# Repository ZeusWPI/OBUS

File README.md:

# Ontmijnen van een Bom vereist Uitstekende Samenwerking

You see an armed time bomb but don't know how to disarm it. Your friends found a manual to defuse the bomb and you have them on call. This is the premise of the game OBUS, a hardware project by [Zeus WPI](https://zeus.ugent.be). Inspired by the amazing software game [Keep Talking and Nobody Explodes](https://www.keeptalkinggame.com/).

## Get started writing a module

These are the instructions for building your own OBUS module with an Arduino Nano v3 and the custom PCB. If
you're using other hardware, you might need to do some things differently.

0. (Read the "[Getting started guide](docs/GETTING_STARTED.md)" to get a general idea of how OBUS works.)
1. [Install](https://www.arduino.cc/en/Guide/#install-the-arduino-desktop-ide) the Arduino IDE.
2. Clone this repository with Git in a permanent location on your drive.
3. Symlink the library: `ln -s /ABSOLUTE/PATH/TO/REPO/lib /PATH/TO/Arduino/libraries/obus`
  (on most Linux distro's, this the Arduino folder is in `$HOME/Arduino`)
4. Follow [these steps](https://github.com/autowp/arduino-mcp2515/#software-usage) to install the CAN library
5. Execute `./src/new_module.sh` to create a new module. When asked for a type, you'll probably want to choose 'puzzle'.
6. Edit the newly generated .ino file, either in the Arduino IDE or in your own editor.
7. In the Arduino IDE, select the correct board (Arduino Nano) and processor (ATmega328P (Old Bootloader)). After that,
   flash your code to the Arduino and test it out.
8. On some Linux distributions, you'll need to prevent BRLTTY from taking over the serial adapter because BRLTTY thinks it's a Braille keyboard. You can do this by uninstalling it (`pacman -R brltty`) or by [disabling it and then rebooting](https://unix.stackexchange.com/questions/670636/unable-to-use-usb-dongle-based-on-usb-serial-converter-chip).
9. If you get permission errors, try adding yourself to the dialout or uucp (Arch Linux) group

## Background
### Game

The game is played by at least two players. The goal is to defuse a bomb,
this is accomplished by defusing every module on that bomb before the bomb
timer runs out.

There are two roles:

- Expert: this person can read the manual about how to defuse the bomb, but cannot see nor interact with the bomb
- Defuser: this person can see and interact with the bomb, but cannot read the manual

These two roles can communicate with each other. To successfully defuse the bomb, they must
communicate efficiently and clearly. If a mistake is made, the team gets a strike.
If they get too many strikes or the timer runs out, the bomb explodes.

## Common wiring between all modules

- CAN-H: red on JST 3 pin connectors, purple on CAN wire
- CAN-L: white on JST 3 pin connectors, brown on CAN wire
- +12V: red on 2 pin JST connector and power wire
- ground: black on 2 pin JST connector, no color on power wire

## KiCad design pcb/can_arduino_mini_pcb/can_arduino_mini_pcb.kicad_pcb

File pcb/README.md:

# OBUS PCB

In order to make it easier for our members to get started creating their own OBUS module,
we designed and ordered PCBs they can use instead of having to wire up the basics
on a breadboard. The PCB accomodates an Arduino Nano V3 (and clones), an MCP2515 CAN-bus module
and an RGB LED. The LED and CAN bus module are connected to pins on the
Arduino Nano. All pins on the Arduino Nano are connected to the ajacent pin socket so
they can easily be accessed when breadboarding.
The pins already used by the OBUS framework are marked with exclamation marks. This does
not mean they can't be used for other purposes anymore, just that you need to pay
attention when using them: for example the SPI pins can be used for other devices, but
the LED pins can't. While picking the pins, we made sure to use the least useful pins
for the OBUS framework: we tried to pick as few PWM pins as possible, didn't pick any I2C
pins, ...

## Connecting the parts on the socket.

We tried our best to make the board as self-explanatory as possible. When pushing the
Arduino into its socket, make sure it's in the correct orientation. When connecting the
CAN bus module, you'll need to flip it on its back, then look at the silk screen on both
the OBUS PCB and the CAN module so that the INT pin is connected in the INT socket hole.

By default, the INT pin on the CAN module is not connected to the Arduino in order to
save pins. If you want to connect the INT pin to pin D2 on the Arduino, you can bridge
the jumper on the top right of the board with some solder.

### Component list per board

- 2 1x15 2.54mm pin sockets, we recommend 4 sockets so you can socket the Arduino as well
- 1 1x07 2.54mm pin socket
- 1 1x02 2.54mm pin socket
- 1 common cathode 5mm RGB LED, pin order RCGB
- 2 330 ohm through hole resistors

## TODO for next board iteration

There is still some space left over at the top and sides of the board, so use it:

- Add extra connection holes for every Arduino pin where wires can be soldered semi permanently on the sides of the board
- Add copper pads/holes to make a "perfboard" on the bottom of the board (with 2.54mm spacing, like a breadboard)
- Add holes to solder wires in for the status RGB LED in case we don't want this on the main PCB
- Add silkscreen with pin names on back of PCB
- Add SMD footprints for LED resistors
- Add holes for M3 bolts
- Add logo on back

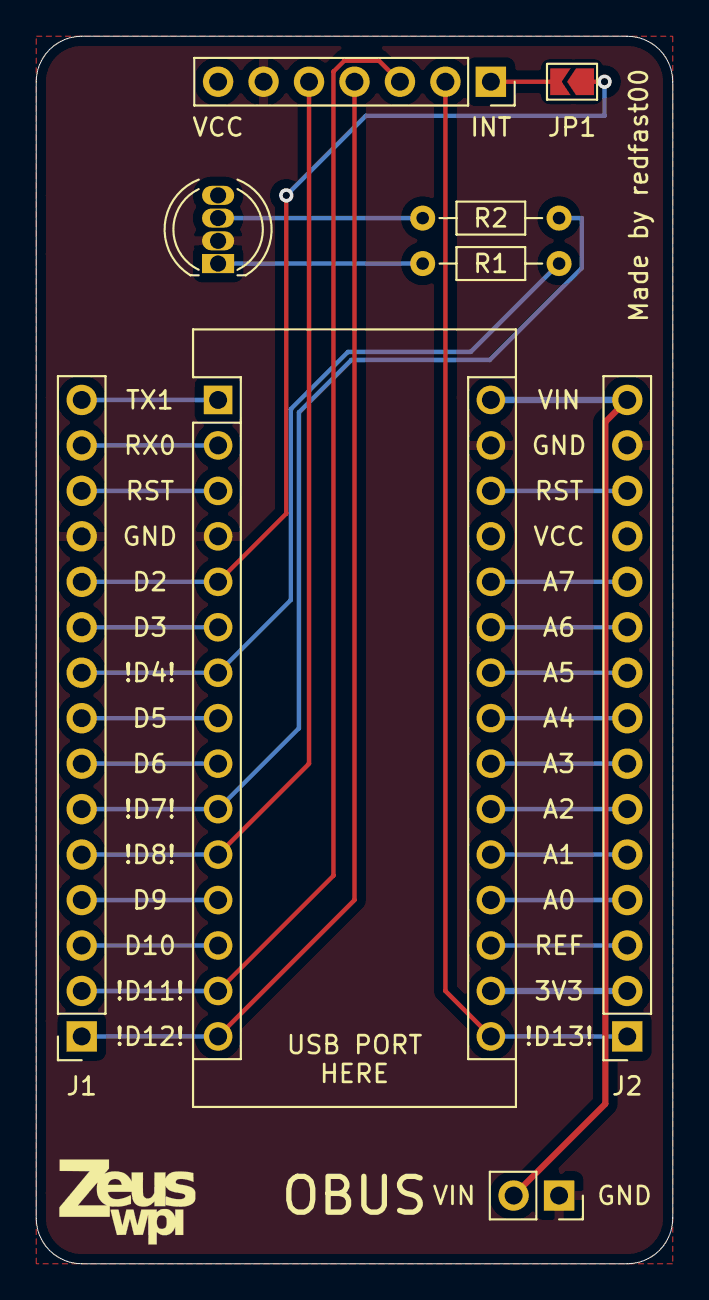
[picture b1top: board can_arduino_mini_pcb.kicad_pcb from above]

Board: 2 copper layers, 35.6 x 68.6 mm, 10 parts (0 on the bottom side), 32 nets.

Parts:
A1: Arduino_Nano_v3.x; Arduino_Nano
D1: LED_RCGB; LED_D5.0mm-4_RGB
J1, J2: Conn_01x15_Female; PinSocket_1x15_P2.54mm_Vertical
J3: Conn_01x02_Female; PinSocket_1x02_P2.54mm_Vertical
J4: Conn_01x07_Female; PinSocket_1x07_P2.54mm_Vertical
JP1: Jumper_NO_Small; SolderJumper-2_P1.3mm_Open_TrianglePad1.0x1.5mm
R1, R2: 330; R_Axial_DIN0204_L3.6mm_D1.6mm_P7.62mm_Horizontal
U1: CAN_MODULE; logo_small

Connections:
+3V3: A1.17, J2.2
+5V: A1.30, J2.15, J3.2
GND: A1.4, A1.29, D1.2, J1.12, J2.14, J3.1, J4.6
unnamed: A1.1, J1.15
unnamed: A1.2, J1.14
unnamed: A1.3, J1.13
unnamed: A1.5, J1.11, JP1.1
unnamed: A1.6, J1.10
unnamed: A1.7, J1.9, R1.2
unnamed: A1.8, J1.8
unnamed: A1.9, J1.7
unnamed: A1.10, J1.6, R2.2
unnamed: A1.11, J1.5, J4.5
unnamed: A1.12, J1.4
unnamed: A1.13, J1.3
unnamed: A1.14, J1.2, J4.3
unnamed: A1.15, J1.1, J4.4
unnamed: A1.16, J2.1, J4.2
unnamed: A1.18, J2.3
unnamed: A1.19, J2.4
unnamed: A1.20, J2.5
unnamed: A1.21, J2.6
unnamed: A1.22, J2.7
unnamed: A1.23, J2.8
unnamed: A1.24, J2.9
unnamed: A1.25, J2.10
unnamed: A1.26, J2.11
unnamed: A1.28, J2.13
unnamed: D1.1, R1.1
unnamed: D1.3, R2.1
unnamed: J4.1, JP1.2
VCC: A1.27, J2.12, J4.7

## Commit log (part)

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2020-08-04 Add README
2020-08-04 Add first draft of OBUS protocol
2020-08-04 Added initial ideas
2020-08-04 Updated ideas
2020-08-04 Upload wireguide tool
2020-08-04 Add idea
2020-08-06 Translate protocol spec, fix inconsistencies
2020-08-06 Translate and enrich ideas
    Besides translation, this commit also incorporates some minor
    clarifications based on what was said on the OBUS codenight.
2020-08-10 Add editorconfig
2020-08-10 Add makefile
2020-08-10 Add CAN example
2020-08-10 Added PoC for catalog
2020-08-10 Start controller code
2020-08-10 Add used can library to readme
2020-08-10 Update catalog styling
2020-08-10 Replaced introduction & overview lorem-text by actual text
2020-08-10 added venv to gitignore
2020-08-10 Implementing hello handshake
2020-08-10 Added dummy controller to catalog
2020-08-10 Added editor folders & venv folder to gitignore
2020-08-10 Added rudimentary HTML generator for catalog
2020-08-10 Added json files for module types
2020-08-10 Updated HTML generator to generate controllers, input-, output- and panic modules
2020-08-10 Implemented discovery round
2020-08-10 Updated generator to generate complete catalog page
2020-08-10 Added generated files to gitignore
2020-08-10 Added extra modules to JSON
2020-08-10 add module code
2020-08-10 Checkpoint before bitvectoring
2020-08-10 Add deubg module that prints everyting on the bus.
2020-08-10 Fix 2 comments in module code
2020-08-10 Add strike count to protocol when signaling one happened
2020-08-10 Not yet tested controller implementation
2020-08-10 enhancements
2020-08-10 Make baudrate higher for more responsive prints
2020-08-12 Add templating to the html
2020-08-15 Update on wireguide
2020-08-15 Correct typo, add priority info
2020-08-16 Start writing web-based debugger
2020-08-18 Fix indentation
2020-08-18 Correct module ID handling: ID only unique per type
2020-08-19 Add debugging Arduino code
2020-08-19 Spaces to tabs
2020-08-20 Finish an obuscan abstraction
2020-08-20 Better initialization
2020-08-20 Update library and stuff
2020-08-20 Library-ish layout
2020-08-24 Update instructions, less subdirs
2020-08-25 Extend protocol with info modules
2020-08-25 Add module template and new_module.sh
2020-08-25 Hardware documentation
2020-08-25 Rename idempotency to count, add to strike msg
2020-08-25 Add module library code
2020-08-25 Template: add module type and ID, correct functions
2020-08-26 Remove example
    Not needed any more: this only exemplifies CAN usage.
2020-08-26 Fix reorganization
2020-08-26 Add more setup steps to the README
2020-08-26 Change library to use callback functions, add basic hardware
2020-08-26 Add basic module with two buttons
2020-08-26 Enable error interrupt
2020-08-27 Different, less efficient way of checking if buffer overflowed
2020-08-27 Cleanup
2020-08-27 Add needy module, clean up code
2020-08-28 Add MIT license, approved by all previous contributors
2020-08-30 Add MOANA page
2020-08-30 Split in different tables, small improvements
2020-08-30 Better intro text
2020-08-30 Add source of inspiration
2020-08-31 Make controller use display
2020-08-31 Restart discovery round if no puzzles are found
2020-08-31 Correct commented setup call in module template
2020-08-31 Add the development IDs as defined by MOANA
2020-08-31 Change loop functions in template
2020-09-07 Add blinkenlight for status
2020-09-07 Add reverse engineered month day selector
2020-09-07 Variable length debugger
2020-09-07 Use pin 8 everywhere
2020-09-07 Fixed shebang and changed the bash4 lowercase command -> tr command
2020-09-07 Added date module
2020-09-07 Resend hello, print number of modules
2020-09-07 Fix controller module count on display
2020-09-07 Add instruction to set up Arduino IDE for uploading
2020-09-07 Fix controller
2020-09-07 Use constant for development ID in modules
2020-09-07 Added support for the MacOS version of find.
2020-09-08 Check sed version instead of OS, dedupe sed script
2020-09-08 Make new_module script POSIX compliant
2020-09-08 Use non-streaming editor and avoid temporary script
2020-09-08 change layout
2020-09-08 cleanup commented code
2020-09-08 add a color identifier for modules
2020-09-08 cleanup server code
2020-09-09 make hiding raw messages more efficient, some tweaks
2020-09-09 Fix typo in solve
2020-09-09 Add info start message
2020-09-09 OOps
2020-09-09 Remove old code
2020-09-09 Change module loop api, add info module
2020-09-09 Only send messages the client hasn't seen before
    We also only keep 200 messages in memory on the server.
2020-09-09 try adding a data class
2020-09-09 Init lcd
2020-09-09 fix everuthigni
2020-09-09 Cleanup code
2020-09-09 remove unused endpoint
2020-09-09 Fix whitespace
2020-09-09 Improve LED in module
2020-09-09 Clean state, use infomessage data length, fix info module lib code
2020-09-09 Don't return None when unknown message type, add new messages for info module
2020-09-09 Add option to only show last state update in series of state updates
2020-09-09 Change char into uint8_t
2020-09-09 Add "module name" in MOANA template
2020-09-09 Assign info module 1 to redfast00
2020-09-10 Add serial number info module
2020-09-10 Set MOANA assigned ID
2020-09-11 Fix wrong class
2020-09-11 Add util functions for byte (un)packing
2020-09-11 Add info phase in controller
2020-09-11 Parse ACKs in debugger
2020-09-11 Implement sending controller ACKs
2020-10-20 Fix swapped comments
2020-10-21 Make CAN error pattern more recognizable
2020-10-22 Extract function
2021-01-30 Add custom PCB
2021-01-30 Add callback for getting info
2021-01-30 Put comments in correct order
2021-01-31 Change RGB LED pins in docs
2021-01-31 Structure modules
2021-02-01 Remove double function
2021-02-01 Make it easier for new people to get started
2021-02-01 Revert "Use non-streaming editor and avoid temporary script"
    This reverts commit 11e5f16425a6015705889a99157abeeb5bcbc035.
2021-02-01 Make info and state optional callbacks
2021-02-01 Remove empty callbacks from modules
2021-02-01 Remove info callback in template, correct casing
2021-02-01 Add deadline for loop function so users are forced to call it frequently
2021-02-01 Add field for amount of puzzle modules connected
2021-02-01 Start game with button instead of automatically
2021-02-01 Make deadline msg somewhat clearer and add comment
2021-02-01 New payload type for gamestart
2021-02-01 Revert "New payload type for gamestart"
    This reverts commit 1743d8d58acbf856b986adb84d32bd59658b6e07.
2021-02-01 Change field from "puzzles solved" to "… left"
2021-02-01 Remove unused constant
2021-02-01 Consistently declare pins with PIN_ constants
2021-02-01 Simplify testmodule
2021-02-01 Fix typos and indentation
2021-02-03 Deterministic modules
2021-05-10 Put more details in getting started guides, fix grammar
2021-05-10 Fix filename
2021-07-31 Add new idea for docs
2021-07-31 Add GitHub action to build docs
2021-07-31 Install texlive-full in builder
2021-07-31 Implement caching in docs build
2021-07-31 Check initialization of CAN module (untested)
2021-07-31 Make sure serial number consists of at least one digit and letter
2021-08-09 Add pressure coupler documentation
2021-08-09 Add ports info module openscad
2022-01-12 Printed version of info port module
2022-01-12 Add future PCB improvement notes
2022-01-17 Properly set length field for controller ACK
2022-01-17 Add ability to send in debugger module
2022-01-17 Add note about brltty to README
2022-01-17 Fix order of operators
2022-01-17 Now that the debugging protocol is binary, don't use readline
2022-01-17 Prepare for Python controller
2022-01-17 Extract message class
2022-01-19 Add time unit to docs, change meaning of ACK
2022-01-19 Add rough draft of Python controller
2022-01-19 Add fallback when seeding random
2022-01-19 Add more puzzle docs
2022-01-19 Add warning that controller is no longer used
2022-01-24 Get controller working + basic interface
2022-01-24 Add CC0 strike sound
2022-01-25 Extrapolate timer, show module state
2022-01-25 Only enable module if it has been acked
2022-01-25 Add button to clear logs
2022-01-25 Fix timeleft calculation
2022-02-01 Get properly started on writing manual
2022-02-01 Change template docs
2022-02-01 Fix wall
2022-02-01 Reverse engineered and wired up R455 timer
2022-02-01 Remove panelized PCB, convert to kicad 6
2022-02-02 PCB idea: add silkscreen with pin names on back
2022-02-03 Disable adding appendix page for now
2022-02-03 Add indicators info module
2022-02-03 Fix directory structure, minor rewording
2022-02-08 Work some more on maze
2022-02-09 brltty is now optional
2022-02-10 Add note about permission error
2022-02-10 C is stupid
2022-02-10 Refactor controller frontend
2022-02-10 Redesign controller page
2022-02-11 Add spectroscopy amplifier (model 2020)
2022-02-11 Add prefix page
2022-02-11 Some more notes for new PCB design
2022-02-11 Download font, fix typo's
2022-02-11 Show strikes on controller
2022-02-15 fix callback_game_start in template
2022-02-15 fix callback_game_start signature
2022-02-15 Exit with exitcode if build failed
2022-02-15 Add controller screenshot, add strike explanation
2022-02-15 Always include csquotes
2022-02-15 Add controller screenshot
2022-02-15 add Counter/Timer model 1772 module
2022-02-21 Add serial module
2022-03-07 Work some more on ports infomodule
2022-03-10 Some more info port updates
2022-03-10 Write some docs for the ports infomodule
2022-03-11 docs
2022-03-11 Wiring info
2022-03-14 add puzzle idea and initial code
2022-03-14 add global vars for buttons
2022-03-14 update rules
2022-03-14 working but no CAN
2022-03-14 add strikes
2022-03-14 fix typos because of bobby <3 xx
2022-03-14 attempt to fix strikes
2022-03-14 Update puzzle_spectroscopy_amplifier.ino
    work on strikes
2022-03-15 sudoku
2022-03-15 authors
2022-03-15 Assign ID 3
2022-03-15 Integrate debugger into controller
2022-03-15 Add more robust error printing
2022-03-15 Remove old debugserver
2022-03-15 add radarlock puzzle/module
2022-03-15 fixed small errors
2022-03-18 Add reset_press_count method to Debounced
2022-03-18 Uncomment CAN
2022-03-18 Turn potentiometer around
2022-03-18 Add needy finetuner
2022-03-18 Finish module code
2022-03-18 Add case
2022-03-18 Add documentation for needy finetuner
2022-03-18 Filters messages on puzzle and needy modules
2022-03-18 Make frontend somewhat fancier
2022-03-19 module puzzle_radarlock
2022-03-19 puzzle radarlock
2022-03-20 Fix callback_game_start and add leds on boundary
2022-03-20 Add stop button
2022-03-20 Final fixes
2022-03-20 Remove log statement
2022-03-20 Add idle animations
2022-03-20 Add other mazes
2022-03-20 Add solve and callback_game_stop
2022-06-19 Avoid collisions in CAN messages
2022-06-19 Fix typo
2022-06-19 Add CAN controller datasheet
2022-06-21 Implement controller-side error detection
2022-06-23 Fix that every message was an error message
2022-06-23 Cookware module
2022-06-23 Move recipe ingredient lists to PROGMEM
2022-06-23 Pin 10 is cursed
2022-06-26 Always use snake_case
2022-06-26 Format code consistently
2022-06-26 Handleiding
2022-06-27 Use multicols to make list of ingredients take up less space
2022-06-27 Reduce debounce time
2022-06-27 Update cookware svgs to actual icons
2023-05-16 Add protocol flow
2023-05-16 Spread out puzzle module hello messages
2023-11-17 Colored words module: don't show same word twice in a row
2023-11-17 Add cookware module to MOANA
2023-11-17 Very basic controller README
2023-11-17 Don't redraw position indicator if not needed to avoid flickering
2023-11-22 Set seed when game starts instead of in infostart phase
2023-11-22 Disable logging of route hits
2023-11-22 Add warning to colored words
2023-11-22 Keep infinite messages, improve performance
2023-11-23 Add warning for readMessage error
2023-11-23 Document is_active
2023-11-23 Reset Arduino when controller starts
2023-11-23 Disable buttons when cookware module is not running
2023-11-23 Preload sounds and cancel alarm when game ends
2023-11-23 Add OpenSCAD designs for cases
2023-11-24 Add ding sound for solved puzzle, show seed
2023-11-24 Oops, forgot to commit templates
2023-11-24 Add puzzle solved sound
